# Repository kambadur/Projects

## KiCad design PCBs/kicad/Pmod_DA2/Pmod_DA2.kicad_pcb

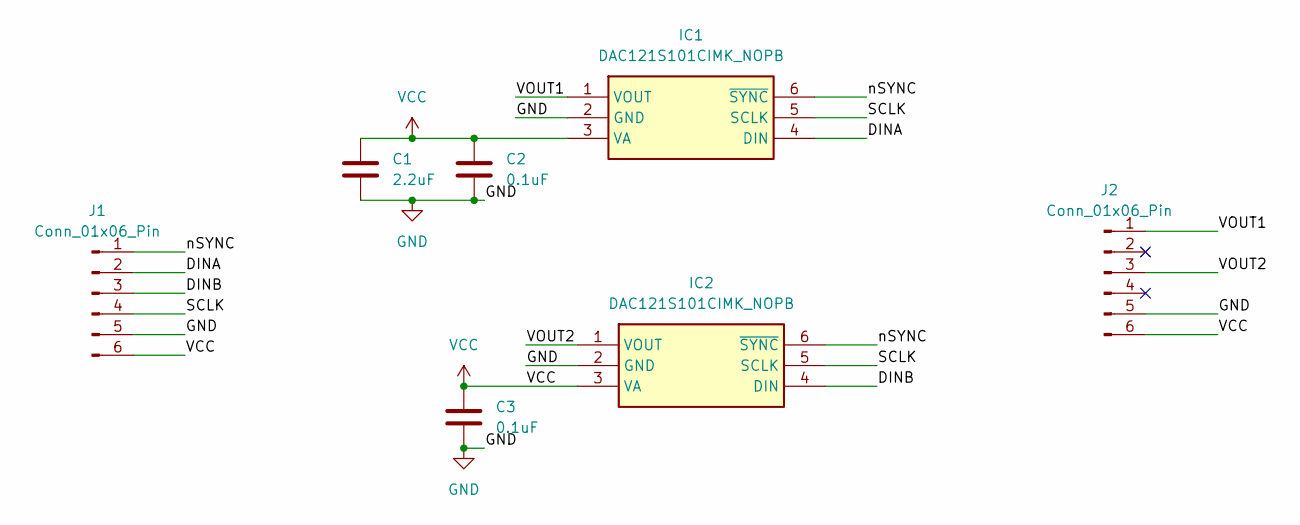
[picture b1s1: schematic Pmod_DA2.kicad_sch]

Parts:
C1: 2.2uF; C_0603_1608Metric
C2, C3: 0.1uF; C_0603_1608Metric
IC1, IC2: DAC121S101CIMK_NOPB; SOT95P280X110-6N; Mouser Part Number 926-DAC121S101CIMKNO
J1: Conn_01x06_Pin; PinHeader_1x06_P2.54mm_Horizontal
J2: Conn_01x06_Pin; PinSocket_1x06_P2.54mm_Horizontal

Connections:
/DINA: IC1.4 (DIN), J1.2
/DINB: IC2.4 (DIN), J1.3
/SCLK: IC1.5 (SCLK), IC2.5 (SCLK), J1.4
/VOUT1: IC1.1 (VOUT), J2.1
/VOUT2: IC2.1 (VOUT), J2.3
/nSYNC: IC1.6 (~SYNC), IC2.6 (~SYNC), J1.1
GND: C1.2, C2.2, C3.2, IC1.2 (GND), IC2.2 (GND), J1.5, J2.5
VCC: C1.1, C2.1, C3.1, IC1.3 (VA), IC2.3 (VA), J1.6, J2.6

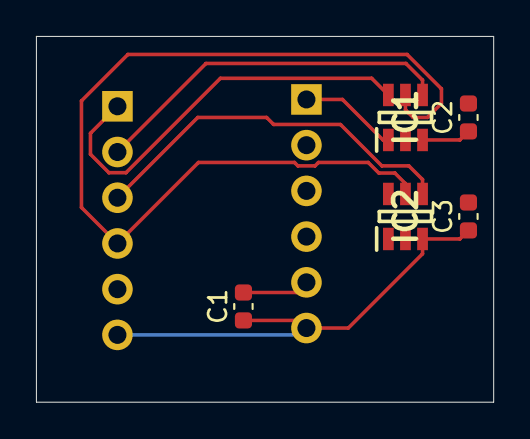
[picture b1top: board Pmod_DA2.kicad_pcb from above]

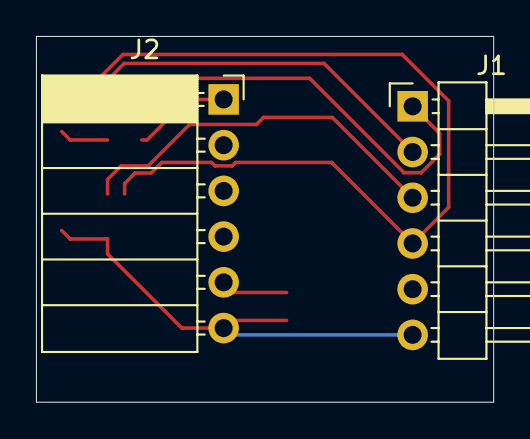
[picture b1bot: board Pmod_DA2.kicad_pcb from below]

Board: 2 copper layers, 25.4 x 20.3 mm, 7 parts (2 on the bottom side), 8 nets.

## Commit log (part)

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2022-05-20 Update readme and assets
2022-05-20 updated assets
2022-05-23 updated scripts
2022-06-02 bug fix update
2022-06-02 Updated readme and assets
2022-06-03 readme and assets updated
2022-06-03 Adder3
2022-06-08 Updated files
2022-06-09 bug fix in the design
    4bit variable assigned to 1bit variable. Only the 0th bit was assgined. In fact I wanted to assign the msb. There were no warnings from the iverilog compiler. Hereafter I have to ber very careful.
2022-06-10 minor modification in the design file
2022-06-10 Create LICENSE
2022-07-29 CaseStudy from the lecture 8: PWM signals for the gate driver are simulated.
2022-07-29 Added model ref file for buck converter to case study simulink file
2022-07-29 Updated case study buck conveter
2022-07-29 updated file name
2022-07-31 Updated case_study_sync_buck conveter model
2022-07-31 Updated case study sync buck converter model
2022-07-31 Week3 Conventional buck converter initial commit
2022-07-31 Model update
2022-08-01 model update conventional buck
2022-08-01 Model update
    Conventional buck converter is added to the main model as a model reference. The model is still open loop.
2022-08-01 Create Conventional_Buck_GateSignal_SWdebounce.slx
    This is full model integrated with conventional buck converter integrated as a model reference. Algebraic loop in the conventional_buck.sly has been resolved using a unit delay block.
2022-08-01 lec13: Practical voltage source
    Ideal voltage source is extended to have finite output resistance and finite bandwidt (output impedance) due to transient load current.
2022-08-02 Update conventional buck converter with practical power supply
2022-08-05 Updated model
2022-08-05 Updated model and parameters
2022-08-05 Update model
    Bug fix in the practical power supply output current. Input converter current (also power supply output current) is obtained by multiplying converter output current with duty ratio.
2022-08-05 Updated model with some more parameter m file switches
    Vref_switch = 0; % switch to turn on Vref transient change
    IL_transient_en = 0; % load current transient enable
    DCM_en = 1; % discontinuous conduction mode enable
    ideal_en = 1; % selection between ideal and practical voltage sources
2022-08-07 updated models
2022-08-08 Updated model with input voltage feed forward for duty cycle adaptation
2022-08-08 feed forward gain parameter introduced
2022-08-08 lecture notes PE_2
2022-08-08 lecture notes PE_1
2022-08-08 updated folder structure
2022-08-08 Open loop and Closed loop controllers are integrated into the simulink model
    Open loop:
    Trailing Edge control with feed forward voltage input
    Closed loop:
    Single loop VMC
    Two loop CMC with feed forward input voltage
2022-08-08 minor updates
2022-08-09 Update Conventional_Buck_practical.slx
    Relational operator for comparator changed from '>=' to '<='. Extra inverter at the output of ~Q terminal in SR flipflop is removed. Still the switch debouncing has issue. It shall be analyzed and fi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
2022-08-09 Share files with lecture TA
2022-08-15 Initial commit DPWM VMC
2022-08-17 Updated callbacks
    1) init_practial_psu_parameters commented out. In this model currently ideal voltage source is considered, This shall be extended shortly.
    2)init_parameters.m: 'tf' commented out. Model uses standard discrete pid controller block. Coefffients are still from the parameter file.
2022-08-17 Updated DPWM VMC model with ADC delay
2022-08-19 lecture notes w3 and w4
2022-08-19 Updated model till lec25 (in progress)
2022-08-19 Updates from lec25
    VMC and CMC both with difference equation based pid controller.
    Quantizer added.
    V0_zoh Out1 port has now V0_init as initial value.
2023-09-11 ses my_workspace projects added
2023-09-11 nrf ses ppi timer event <-> led task added
2023-09-11 nrf ses ppi button event <-> led task project added
2023-09-12 started to write pwm measure ppi
2024-12-30 Vivado project for SPI Controller for AD7303
2024-12-31 docu update
2025-01-11 default case added
2025-01-31 i2c controller initial commit
2025-07-07 FSM improved. SyyClk at 100MHz. SPI Clock at 1MHz. Can be tested on a Basys3 board.
2025-07-07 updated testbench
2025-11-01 fa_custom_axi_lite_slv_1 on zedboard. both vivado and vitis projects.
2026-01-15 .gitignore commit
2026-01-16 Vivado repo from t440p
2026-01-16 Vitis repo from t440p
2026-01-16 rp2040_exercises repo from t440p
2026-01-16 spi_controller_test repo from t440p
2026-01-16 Projects repo from t440p
2026-03-08 commit from t440p
